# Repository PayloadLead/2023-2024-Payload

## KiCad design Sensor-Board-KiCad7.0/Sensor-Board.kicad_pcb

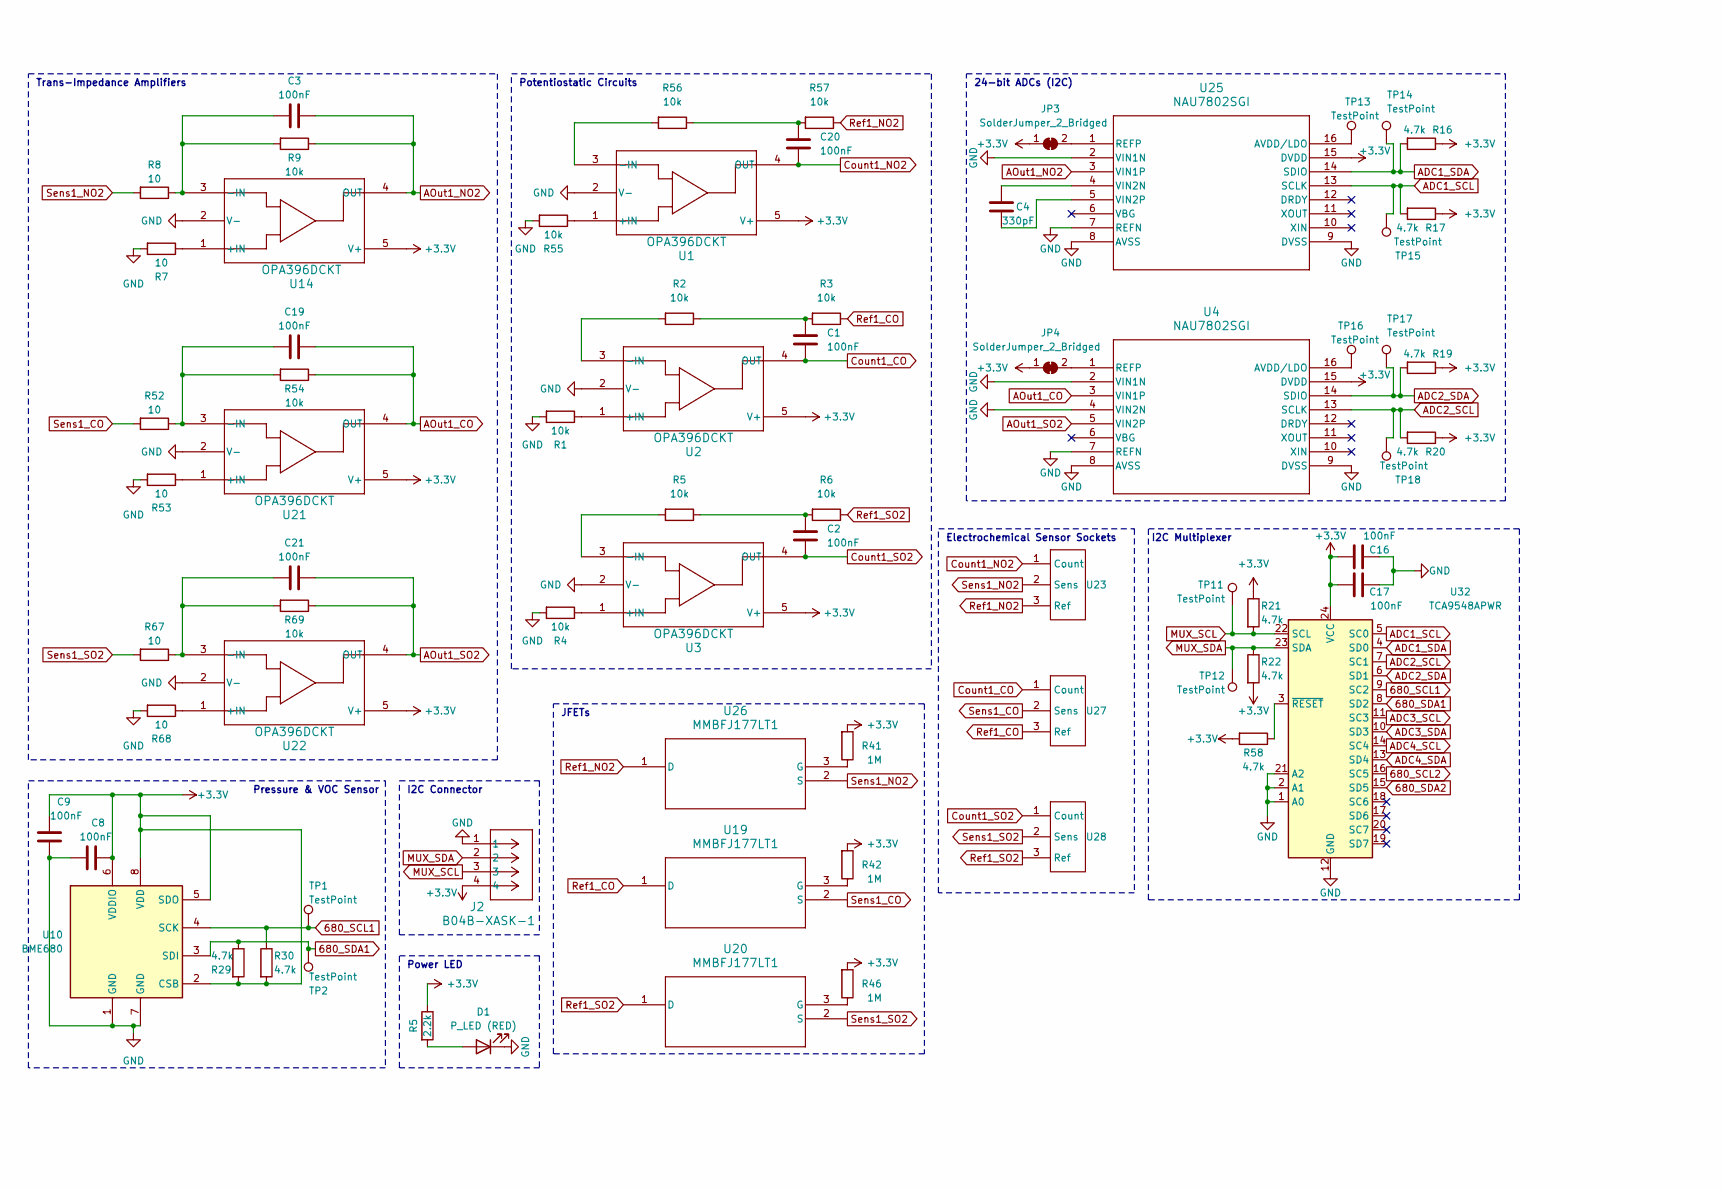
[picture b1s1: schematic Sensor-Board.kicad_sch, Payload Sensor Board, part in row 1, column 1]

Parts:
C1, C2, C3, C8, C9, C16, C17, C19, C20, C21: 100nF; C_0603_1608Metric; LCSC C14663
C4: 330pF; C_0603_1608Metric; LCSC C140966
D1: P_LED (RED); LED_0603_1608Metric_Pad1.05x0.95mm_HandSolder
J2: B04B-XASK-1; CONN_B04B-XASK-1_JST; LCSC C264994
JP3, JP4: SolderJumper_2_Bridged; SolderJumper-2_P1.3mm_Bridged_RoundedPad1.0x1.5mm
R1, R2, R3, R4, R5, R6, R9, R54, R55, R56, R57, R69: 10k; R_0603_1608Metric; LCSC C25804
R7, R8, R52, R53, R67, R68: 10; R_0603_1608Metric; LCSC C22859
R16, R17, R19, R20, R21, R22, R29, R30: 4.7k; R_0603_1608Metric
R41, R42, R46: 1M; R_0603_1608Metric; LCSC C22935
R58: 4.7k; R_0603_1608Metric; LCSC C23162
TP1, TP2, TP11, TP12, TP13, TP14, TP15, TP16, TP17, TP18: TestPoint; TestPoint_Pad_D1.5mm
U1, U2, U3, U14, U21, U22: OPA396DCKT; SC_96DCKT_TEX; Digikey 296-OPA396DCKRCT-ND
U4, U25: NAU7802SGI; SOI16_NAU7802SGI_NUV; Digikey NAU7802SGI-ND
U10: BME680; Bosch_LGA-8_3x3mm_P0.8mm_ClockwisePinNumbering; LCSC C125972
U19, U20, U26: MMBFJ177LT1; SOT-23-3_1P4X3P040_ONS; LCSC C106763
U23: 3-pin socket; Digikey ED90102-ND
U27, U28: 3-pin socket
U32: TCA9548APWR; TSSOP-24_4.4x7.8mm_P0.65mm; LCSC C130026

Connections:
680_SCL1: R30.1, TP1.1, U10.4 (SCK), U32.9 (SC2)
680_SCL2: U32.16 (SC5); also elsewhere on the board
680_SDA1: R29.1, TP2.1, U10.3 (SDI), U32.8 (SD2)
680_SDA2: U32.15 (SD5); also elsewhere on the board
ADC1_SCL: R17.2, TP15.1, U25.13 (SCLK), U32.5 (SC0)
ADC1_SDA: R16.2, TP14.1, U25.14 (SDIO), U32.4 (SD0)
ADC2_SCL: R20.2, TP18.1, U4.13 (SCLK), U32.7 (SC1)
ADC2_SDA: R19.2, TP17.1, U4.14 (SDIO), U32.6 (SD1)
ADC3_SCL: U32.11 (SC3); also elsewhere on the board
ADC3_SDA: U32.10 (SD3); also elsewhere on the board
ADC4_SCL: U32.14 (SC4); also elsewhere on the board
ADC4_SDA: U32.13 (SD4); also elsewhere on the board
AOut1_CO: C19.1, R54.1, U4.3 (VIN1P), U21.4 (OUT)
AOut1_NO2: C3.1, R9.1, U14.4 (OUT), U25.3 (VIN1P)
AOut1_SO2: C21.1, R69.1, U4.5 (VIN2P), U22.4 (OUT)
Count1_CO: C1.2, U2.4 (OUT), U27.1 (Count)
Count1_NO2: C20.2, U1.4 (OUT), U23.1 (Count)
Count1_SO2: C2.2, U3.4 (OUT), U28.1 (Count)
GND: C8.1, C9.2, C16.1, C17.1, D1.1 (K), J2.1, R1.2, R4.2, R7.2, R53.2, R55.2, R68.2, U1.2 (V-), U2.2 (V-), U3.2 (V-), U4.2 (VIN1N), U4.4 (VIN2N), U4.7 (REFN), U4.8 (AVSS), U4.9 (DVSS), U10.1 (GND), U10.7 (GND), U14.2 (V-), U21.2 (V-), U22.2 (V-), U25.2 (VIN1N), U25.7 (REFN), U25.8 (AVSS), U25.9 (DVSS), U32.1 (A0), U32.2 (A1), U32.12 (GND), U32.21 (A2); also elsewhere on the board
MUX_SCL: J2.3, R21.2, TP11.1, U32.22 (SCL)
MUX_SDA: J2.2, R22.1, TP12.1, U32.23 (SDA)
unnamed: C1.1, R2.1, R3.2
unnamed: C20.1, R56.1, R57.2
unnamed: JP3.2 (B), U25.1 (REFP)
unnamed: JP4.2 (B), U4.1 (REFP)
unnamed: R55.1, U1.1 (+IN)
unnamed: R56.2, U1.3 (-IN)
unnamed: R1.1, U2.1 (+IN)
unnamed: R2.2, U2.3 (-IN)
unnamed: R4.1, U3.1 (+IN)
unnamed: TP16.1, U4.16 (AVDD/LDO)
unnamed: R7.1, U14.1 (+IN)
unnamed: C3.2, R8.1, R9.2, U14.3 (-IN)
unnamed: R42.1, U19.3 (G)
unnamed: R46.1, U20.3 (G)
unnamed: R53.1, U21.1 (+IN)
unnamed: C19.2, R52.1, R54.2, U21.3 (-IN)
unnamed: R68.1, U22.1 (+IN)
unnamed: C21.2, R67.1, R69.2, U22.3 (-IN)
unnamed: TP13.1, U25.16 (AVDD/LDO)
unnamed: C4.1, U25.4 (VIN2N)
unnamed: C4.2, U25.5 (VIN2P)
unnamed: R41.1, U26.3 (G)
unnamed: R58.1, U32.3 (~RESET)
Ref1_CO: R3.1, U19.1 (D), U27.3 (Ref)
Ref1_NO2: R57.1, U23.3 (Ref), U26.1 (D)
Ref1_SO2: R6.1, U20.1 (D), U28.3 (Ref)
Sens1_CO: R52.2, U19.2 (S), U27.2 (Sens)
Sens1_NO2: R8.2, U23.2 (Sens), U26.2 (S)
Sens1_SO2: R67.2, U20.2 (S), U28.2 (Sens)

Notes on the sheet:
I2C Connector
JFETs
Electrochemical Sensor Sockets
Power LED
24-bit ADCs (I2C)
Potentiostatic Circuits
I2C Multiplexer
Pressure & VOC Sensor
Trans-Impedance Amplifiers

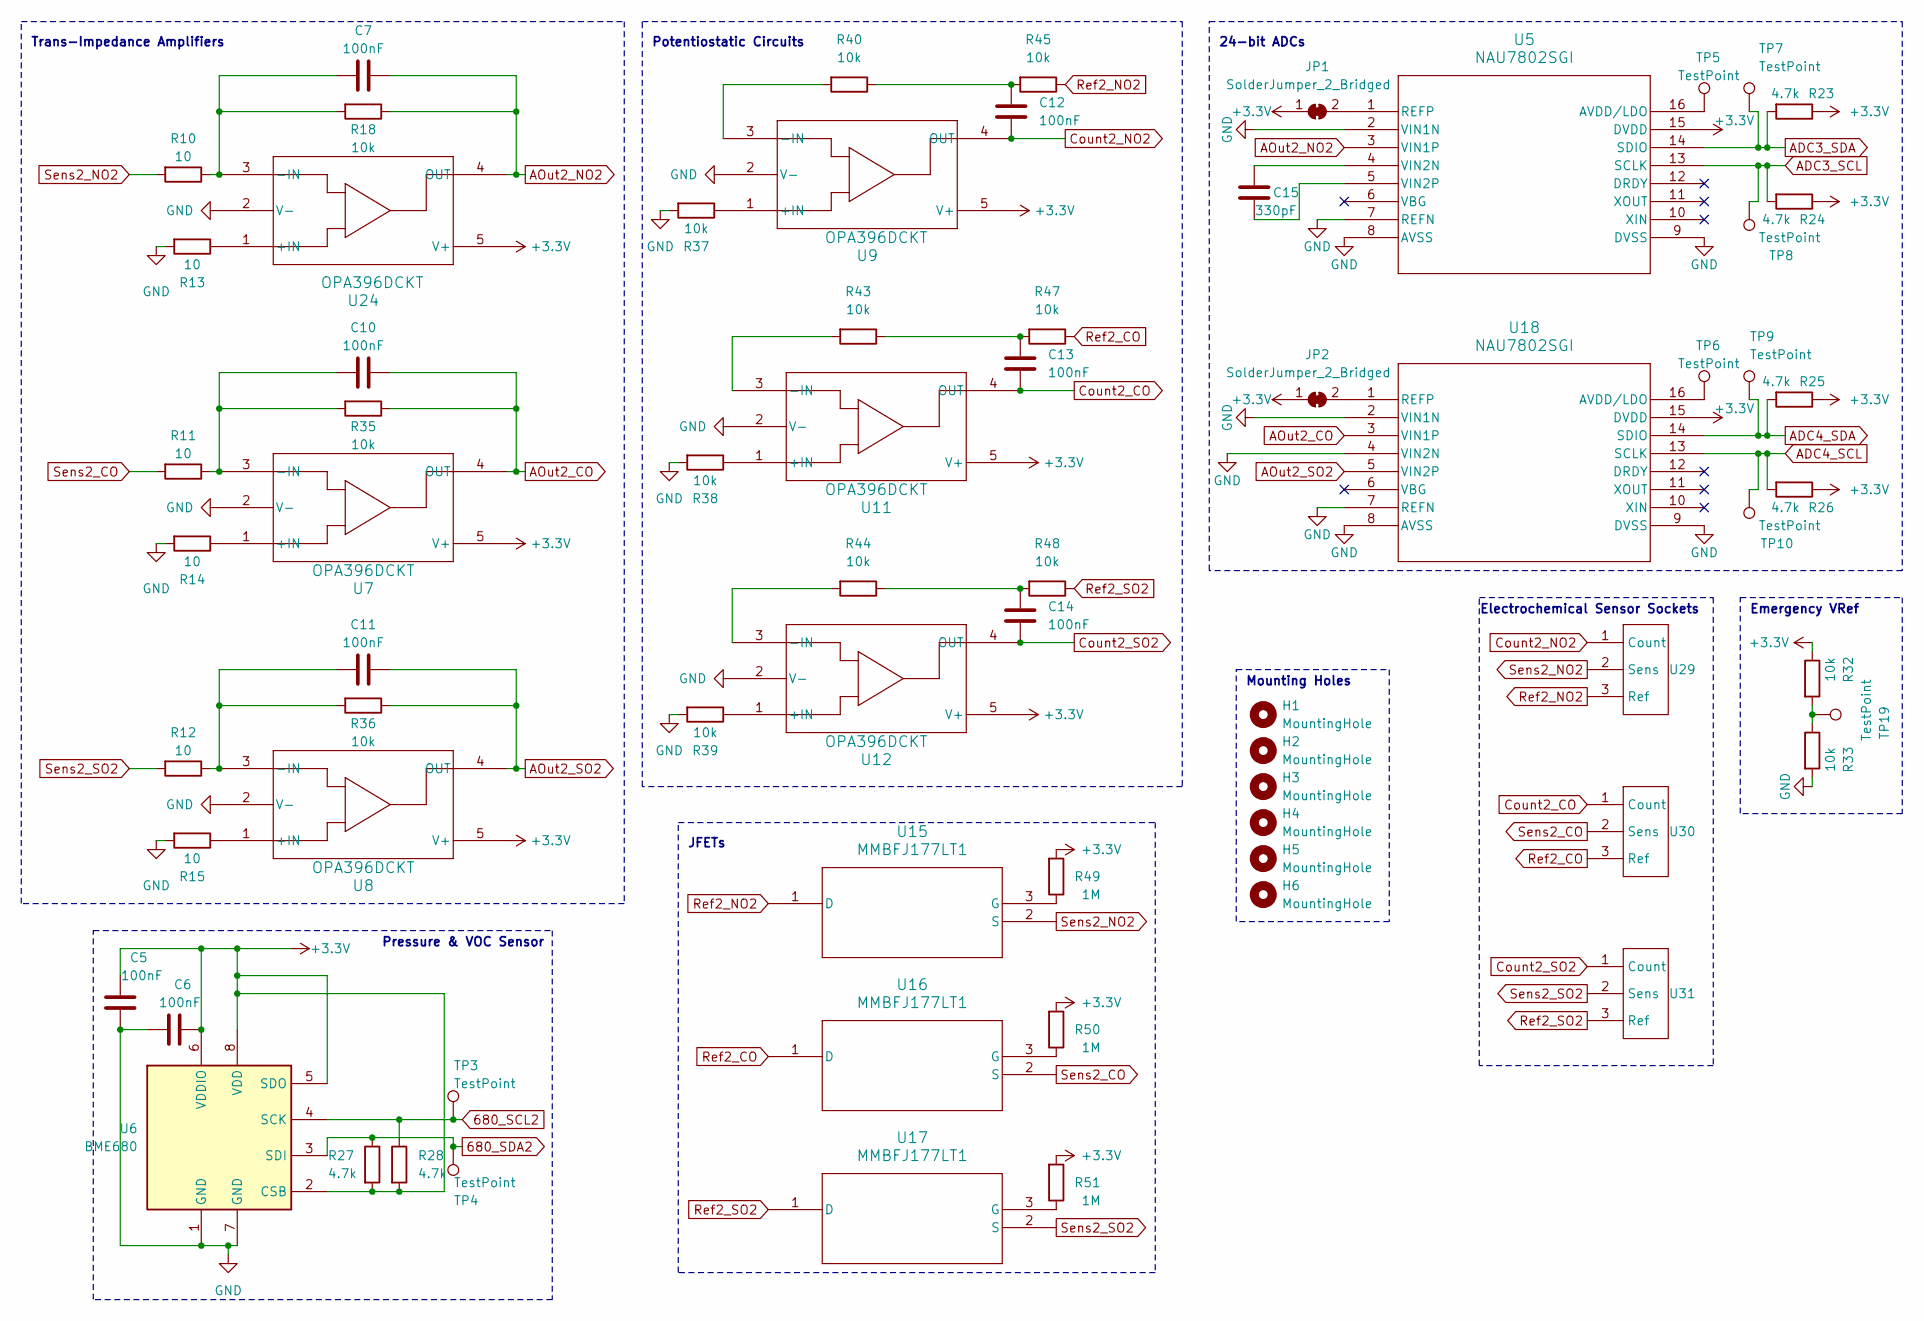
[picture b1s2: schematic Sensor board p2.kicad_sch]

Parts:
C5, C6, C7, C10, C11, C12, C13, C14: 100nF; C_0603_1608Metric; LCSC C14663
C15: 330pF; C_0603_1608Metric; LCSC C140966
H1, H2, H3, H4, H5, H6: MountingHole; Rod_Mounting_Hole_6.7564mm
JP1, JP2: SolderJumper_2_Bridged; SolderJumper-2_P1.3mm_Bridged_RoundedPad1.0x1.5mm
R10, R11, R12, R13, R14, R15: 10; R_0603_1608Metric; LCSC C22859
R18, R35, R36, R37, R38, R39, R40, R43, R44, R45, R47, R48: 10k; R_0603_1608Metric; LCSC C25804
R23, R24, R25, R26, R27, R28: 4.7k; R_0603_1608Metric
R32, R33: 10k; R_0603_1608Metric
R49, R50, R51: 1M; R_0603_1608Metric; LCSC C22935
TP3, TP4, TP5, TP6, TP7, TP8, TP9, TP10, TP19: TestPoint; TestPoint_Pad_D1.5mm
U5, U18: NAU7802SGI; SOI16_NAU7802SGI_NUV; Digikey NAU7802SGI-ND
U6: BME680; Bosch_LGA-8_3x3mm_P0.8mm_ClockwisePinNumbering; LCSC C125972
U7, U8, U9, U11, U12, U24: OPA396DCKT; SC_96DCKT_TEX; Digikey 296-OPA396DCKRCT-ND
U15, U16, U17: MMBFJ177LT1; SOT-23-3_1P4X3P040_ONS; LCSC C106763
U29, U30, U31: 3-pin socket; Digikey ED90102-ND

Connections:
680_SCL2: R28.1, TP3.1, U6.4 (SCK); also elsewhere on the board
680_SDA2: R27.1, TP4.1, U6.3 (SDI); also elsewhere on the board
ADC3_SCL: R24.2, TP8.1, U5.13 (SCLK); also elsewhere on the board
ADC3_SDA: R23.2, TP7.1, U5.14 (SDIO); also elsewhere on the board
ADC4_SCL: R26.2, TP10.1, U18.13 (SCLK); also elsewhere on the board
ADC4_SDA: R25.2, TP9.1, U18.14 (SDIO); also elsewhere on the board
AOut2_CO: C10.1, R35.1, U7.4 (OUT), U18.3 (VIN1P)
AOut2_NO2: C7.1, R18.1, U5.3 (VIN1P), U24.4 (OUT)
AOut2_SO2: C11.1, R36.1, U8.4 (OUT), U18.5 (VIN2P)
Count2_CO: C13.2, U11.4 (OUT), U30.1 (Count)
Count2_NO2: C12.2, U9.4 (OUT), U29.1 (Count)
Count2_SO2: C14.2, U12.4 (OUT), U31.1 (Count)
GND: C5.2, C6.1, R13.2, R14.2, R15.2, R33.2, R37.2, R38.2, R39.2, U5.2 (VIN1N), U5.7 (REFN), U5.8 (AVSS), U5.9 (DVSS), U6.1 (GND), U6.7 (GND), U7.2 (V-), U8.2 (V-), U9.2 (V-), U11.2 (V-), U12.2 (V-), U18.2 (VIN1N), U18.4 (VIN2N), U18.7 (REFN), U18.8 (AVSS), U18.9 (DVSS), U24.2 (V-); also elsewhere on the board
unnamed: C12.1, R40.1, R45.2
unnamed: C13.1, R43.1, R47.2
unnamed: C14.1, R44.1, R48.2
unnamed: JP1.2 (B), U5.1 (REFP)
unnamed: JP2.2 (B), U18.1 (REFP)
unnamed: R32.2, R33.1, TP19.1
unnamed: TP5.1, U5.16 (AVDD/LDO)
unnamed: C15.1, U5.4 (VIN2N)
unnamed: C15.2, U5.5 (VIN2P)
unnamed: R14.1, U7.1 (+IN)
unnamed: C10.2, R11.1, R35.2, U7.3 (-IN)
unnamed: R15.1, U8.1 (+IN)
unnamed: C11.2, R12.1, R36.2, U8.3 (-IN)
unnamed: R37.1, U9.1 (+IN)
unnamed: R40.2, U9.3 (-IN)
unnamed: R38.1, U11.1 (+IN)
unnamed: R43.2, U11.3 (-IN)
unnamed: R39.1, U12.1 (+IN)
unnamed: R44.2, U12.3 (-IN)
unnamed: R49.1, U15.3 (G)
unnamed: R50.1, U16.3 (G)
unnamed: R51.1, U17.3 (G)
unnamed: TP6.1, U18.16 (AVDD/LDO)
unnamed: R13.1, U24.1 (+IN)
unnamed: C7.2, R10.1, R18.2, U24.3 (-IN)
Ref2_CO: R47.1, U16.1 (D), U30.3 (Ref)
Ref2_NO2: R45.1, U15.1 (D), U29.3 (Ref)
Ref2_SO2: R48.1, U17.1 (D), U31.3 (Ref)
Sens2_CO: R11.2, U16.2 (S), U30.2 (Sens)
Sens2_NO2: R10.2, U15.2 (S), U29.2 (Sens)
Sens2_SO2: R12.2, U17.2 (S), U31.2 (Sens)

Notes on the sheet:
JFETs
Potentiostatic Circuits
24-bit ADCs
Emergency VRef
Electrochemical Sensor Sockets
Pressure & VOC Sensor
Trans-Impedance Amplifiers
Mounting Holes

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
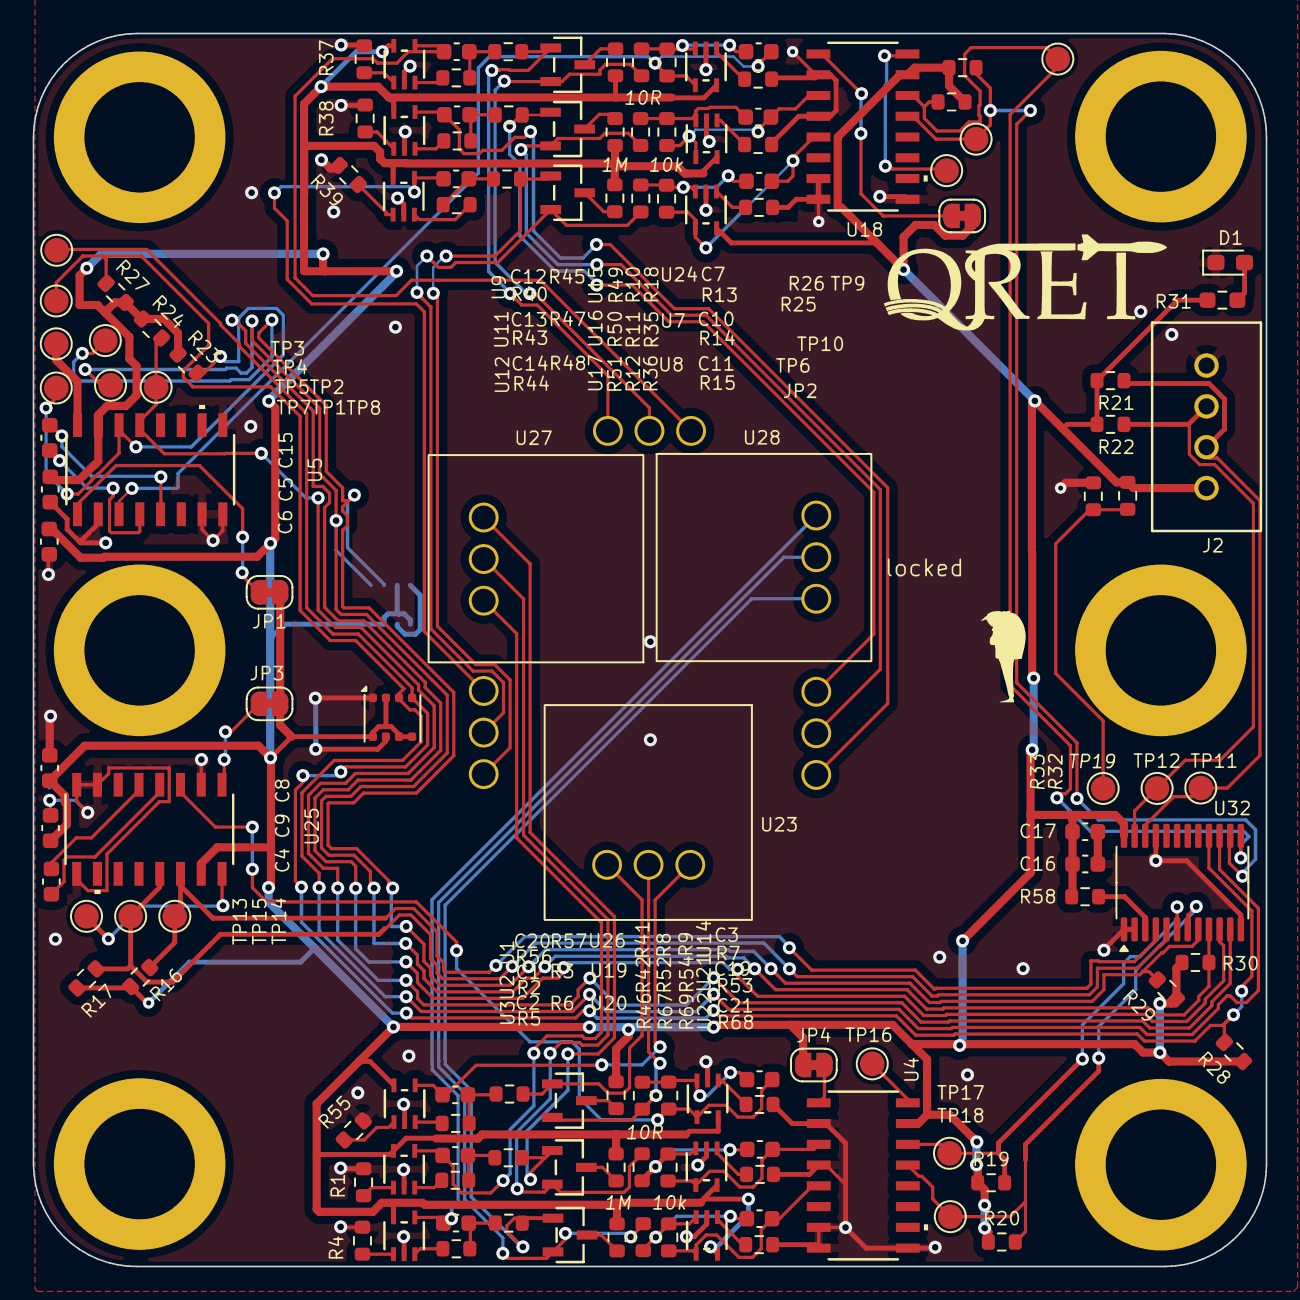
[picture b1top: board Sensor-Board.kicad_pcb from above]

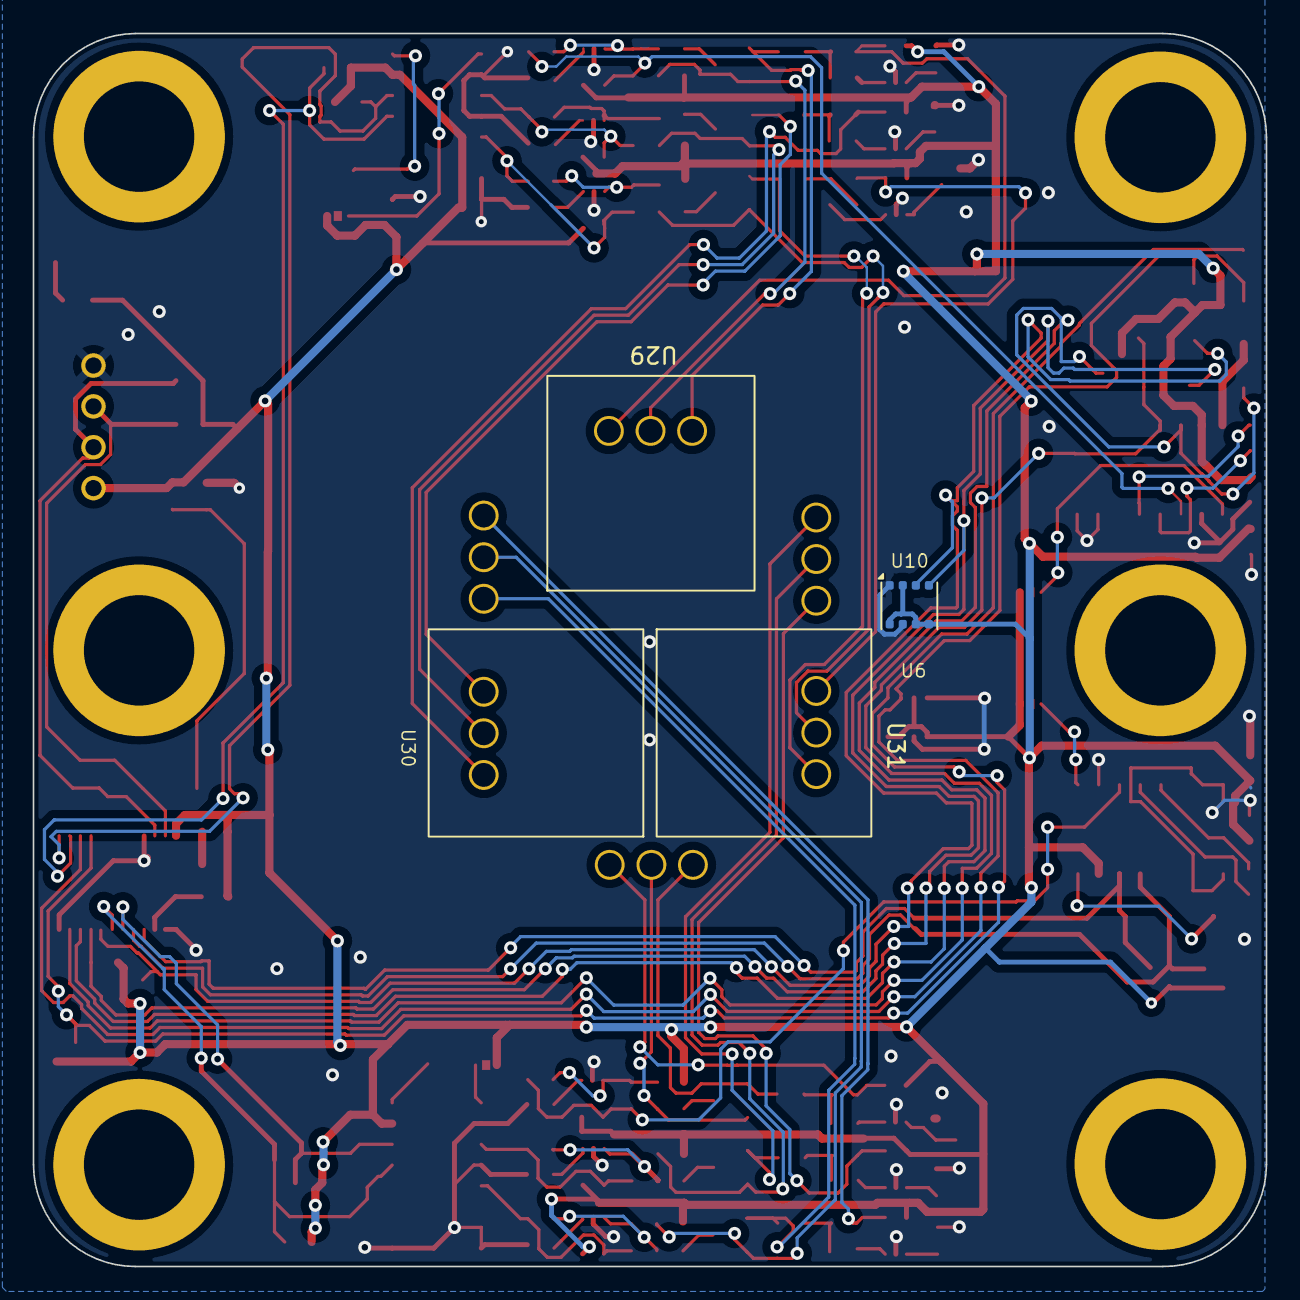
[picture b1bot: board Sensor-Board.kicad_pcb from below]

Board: 2 copper layers, 75.4 x 75.4 mm, 142 parts (4 on the bottom side), 91 nets.

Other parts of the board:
R31: 2.2k; R_0603_1608Metric_Pad0.98x0.95mm_HandSolder

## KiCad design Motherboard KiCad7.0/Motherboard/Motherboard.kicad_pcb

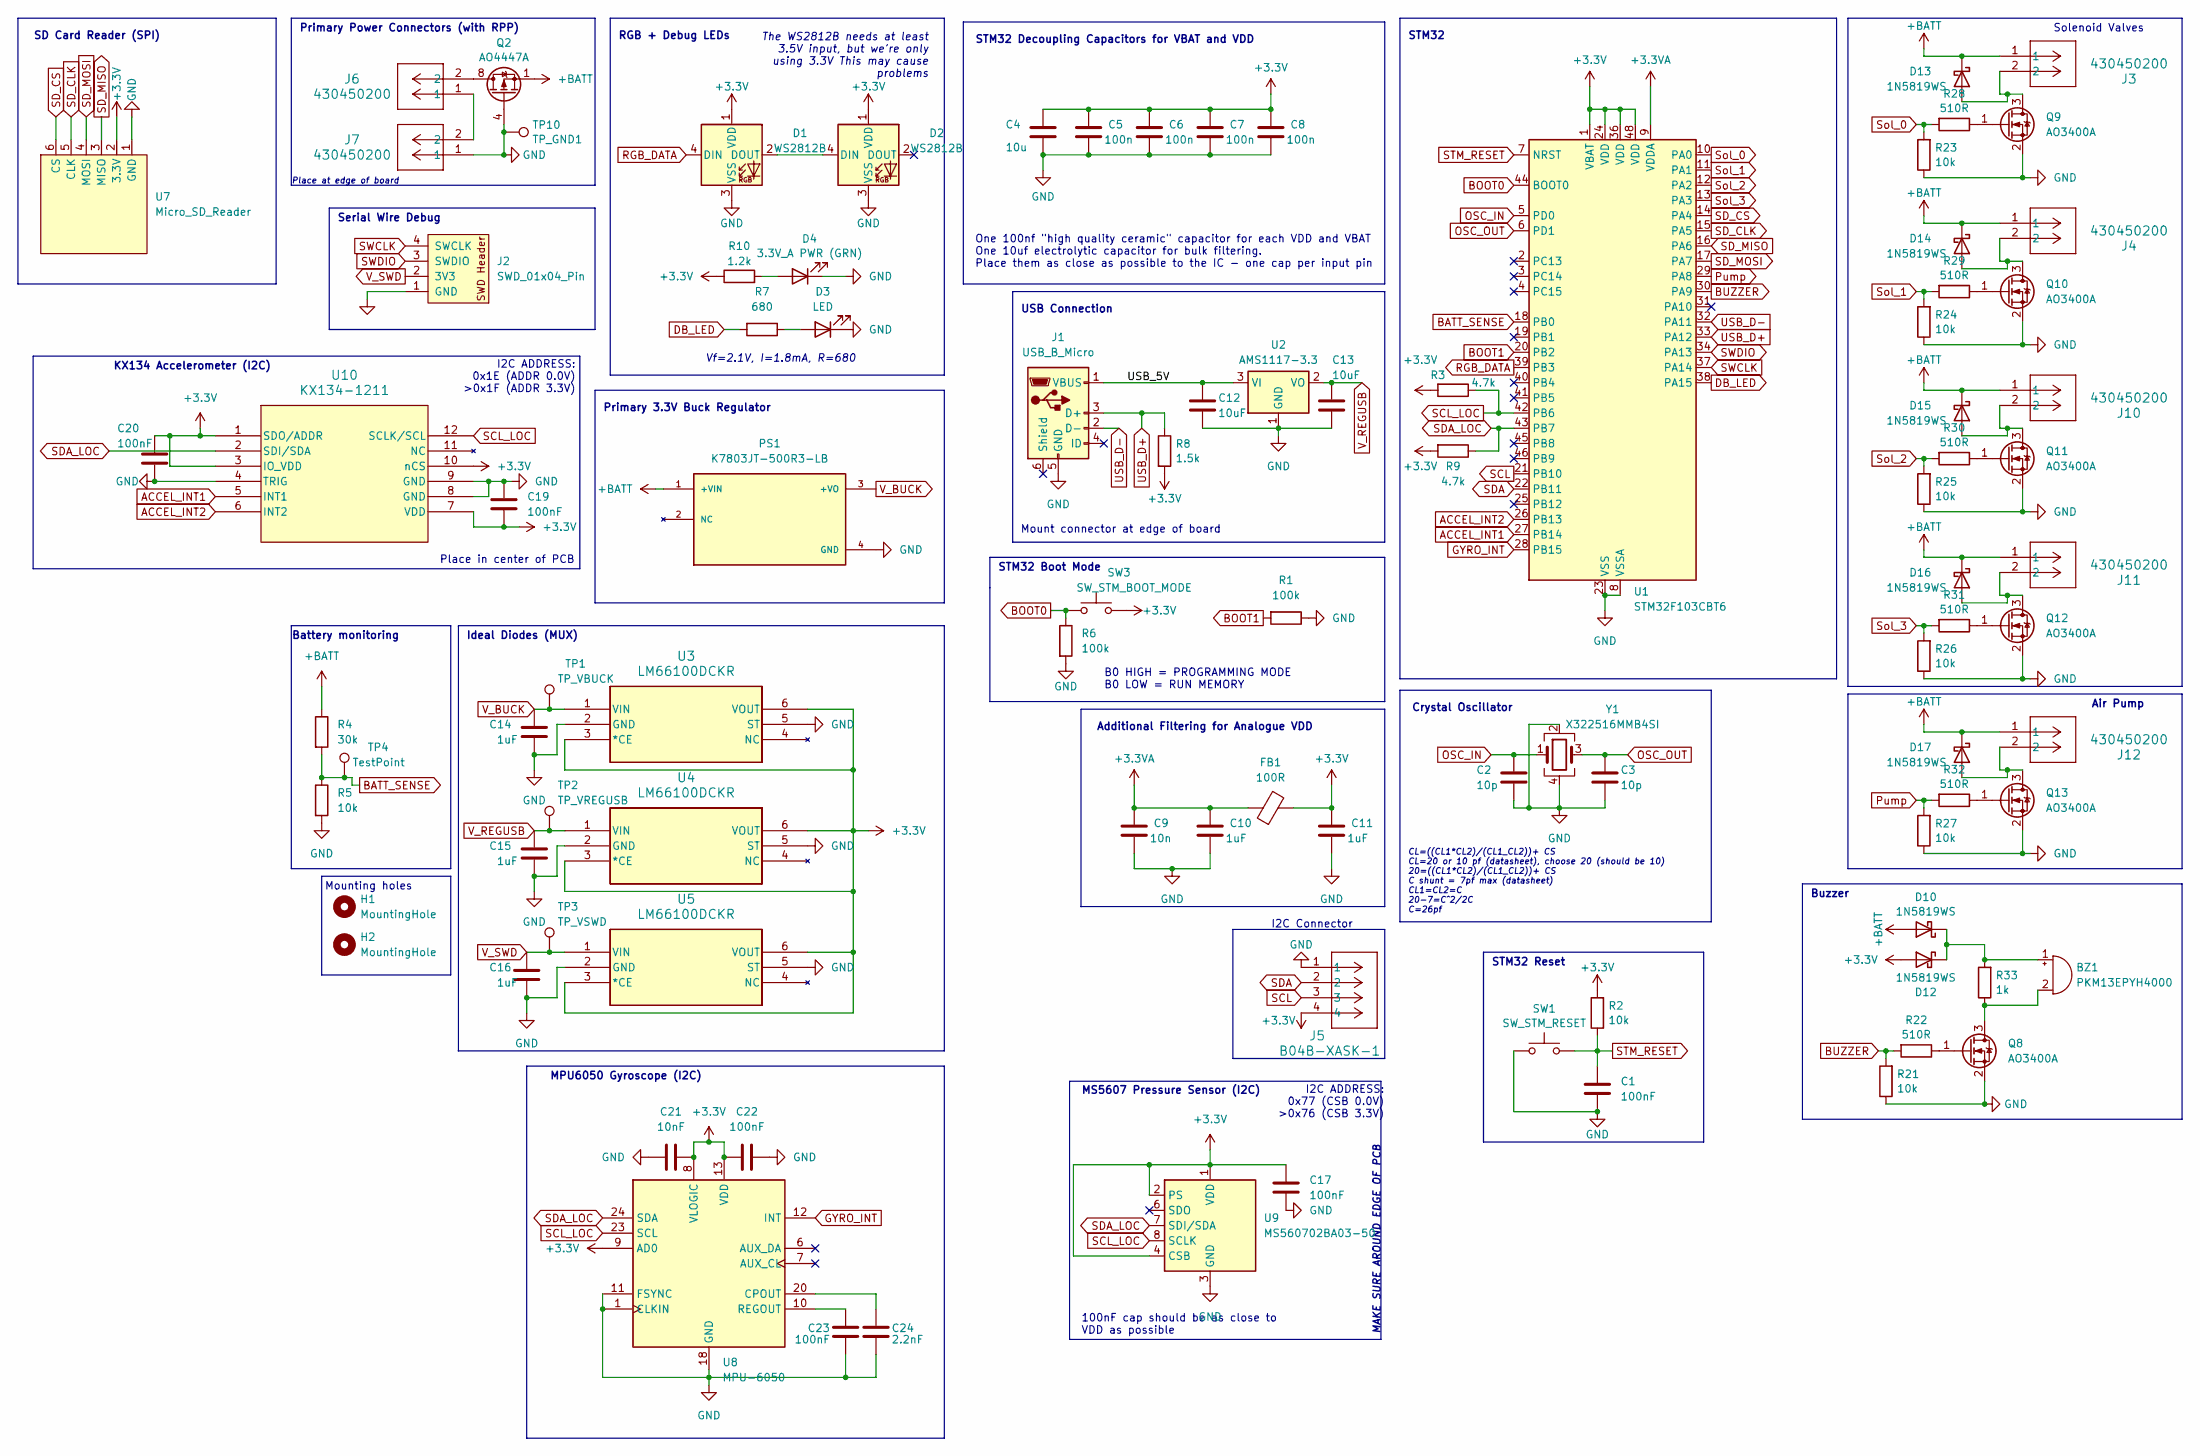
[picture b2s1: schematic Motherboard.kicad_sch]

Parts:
BZ1: PKM13EPYH4000; Buzzer_12.6x9.5RM5.0; Digikey 490-4698-1-ND
C1, C17, C19, C20, C22, C23: 100nF; C_0603_1608Metric; LCSC C14663
C2, C3: 10p; C_0603_1608Metric; LCSC C1634
C4: 10u; CP_Elec_4x5.4; Digikey 732-8411-1-ND
C5, C6, C7, C8: 100n; C_0402_1005Metric; LCSC C1525
C9: 10n; C_0603_1608Metric; LCSC C57112
C10, C11: 1uF; C_0805_2012Metric; LCSC C28323
C12, C13: 10uF; C_0603_1608Metric; LCSC C96446
C14, C15, C16: 1uF; C_0603_1608Metric; LCSC C15849
C21: 10nF; C_0603_1608Metric; LCSC C57112
C24: 2.2nF; C_0603_1608Metric; LCSC C1604
D1, D2: WS2812B; LED_WS2812B_PLCC4_5.0x5.0mm_P3.2mm; Digikey 1568-COM-16347CT-ND
D3: LED; LED_0603_1608Metric; LCSC C72038
D4: 3.3V_A PWR (GRN); LED_0805_2012Metric; LCSC C2297
D10, D12, D13, D14, D15, D16, D17: 1N5819WS; D_SOD-323; LCSC C191023
FB1: 100R; R_0805_2012Metric; LCSC C1015
H1, H2: MountingHole; Rod_Mounting_Hole_6.7564mm
J1: USB_B_Micro; USB_Micro-B_Amphenol_10118194_Horizontal; LCSC C132563
J2: SWD_01x04_Pin; SWD_PinHeader_1x04_P2.54mm_Horizontal; Digikey 2057-PH1RB-04-UA-ND
J3, J4, J6, J7, J10, J11, J12: 430450200; CON_430450200_MOL; LCSC C122431
J5: B04B-XASK-1; CONN_B04B-XASK-1_JST; Digikey 455-B04B-XASK-1-ND
PS1: K7803JT-500R3-LB; K78_JT-500R3_MNS; PARTREV 2022.07.25-A/4; Digikey 2725-K7803JT-500R3-LBCT-ND
Q2: AO4447A; SOIC-8_3.9x4.9mm_P1.27mm; LCSC C125867
Q8, Q9, Q10, Q11, Q12, Q13: AO3400A; SOT-23; LCSC C20917
R1, R6: 100k; R_0603_1608Metric; LCSC C25803
R2, R5, R21, R23, R24, R25, R26, R27: 10k; R_0603_1608Metric; LCSC C25804
R3, R9: 4.7k; R_0603_1608Metric; LCSC C23162
R4: 30k; R_0603_1608Metric; LCSC C22984
R7: 680; R_0603_1608Metric; LCSC C23228
R8: 1.5k; R_0603_1608Metric; LCSC C22843
R10: 1.2k; R_0603_1608Metric; LCSC C22765
R22, R28, R29, R30, R31, R32: 510R; R_0603_1608Metric; LCSC C23193
R33: 1k; R_0603_1608Metric; LCSC C21190
SW1: SW_STM_RESET; SW_Push_1P1T_XKB_TS-1187A; LCSC C318884
SW3: SW_STM_BOOT_MODE; SW_Push_1P1T_XKB_TS-1187A; LCSC C318884
TP1: TP_VBUCK; TestPoint_Pad_1.5x1.5mm
TP2: TP_VREGUSB; TestPoint_Pad_1.5x1.5mm
TP3: TP_VSWD; TestPoint_Pad_1.5x1.5mm
TP4: TestPoint; TestPoint_Pad_1.0x1.0mm
TP10: TP_GND1; TestPoint_Pad_2.0x2.0mm
U1: STM32F103CBT6; LQFP-48_7x7mm_P0.5mm; LCSC C8304
U2: AMS1117-3.3; SOT-223-3_TabPin2; LCSC C6186
U3, U4, U5: LM66100DCKR; SC-70-6_Handsoldering; LCSC C2869734
U7: Micro_SD_Reader; MicroSD Card Reader
U8: MPU-6050; InvenSense_QFN-24_4x4mm_P0.5mm; LCSC C24112
U9: MS560702BA03-50; MS5607_Handsolder; Digikey 223-1198-1-ND
U10: KX134-1211; LGA-12_2x2mm_P0.5mm; LCSC C2157908
Y1: X322516MMB4SI; Crystal_SMD_3225-4Pin_3.2x2.5mm; LCSC C13738

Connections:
+3.3V: C4.1, C5.1, C6.1, C7.1, C8.1, C11.1, C17.1, C19.2, C20.1, C21.2, C22.1, D1.1 (VDD), D2.1 (VDD), D12.2 (A), FB1.2, J5.4, R2.2, R3.2, R8.2, R9.2, R10.1, SW3.3 (B), SW3.4 (B), U1.1 (VBAT), U1.24 (VDD), U1.36 (VDD), U1.48 (VDD), U3.3 (*CE), U3.6 (VOUT), U4.3 (*CE), U4.6 (VOUT), U5.3 (*CE), U5.6 (VOUT), U7.2 (3.3V), U8.8 (VLOGIC), U8.9 (AD0), U8.13 (VDD), U9.1 (VDD), U9.2 (PS), U9.4 (CSB), U9.5 (CSB), U10.1 (SDO/ADDR), U10.3 (IO_VDD), U10.7 (VDD), U10.10 (nCS)
+3.3VA: C9.1, C10.1, FB1.1, U1.9 (VDDA)
+BATT: D10.2 (A), D13.1 (K), D14.1 (K), D15.1 (K), D16.1 (K), D17.1 (K), J3.1, J4.1, J10.1, J11.1, J12.1, PS1.1 (+VIN), Q2.1 (S), Q2.2 (S), Q2.3 (S), R4.1
/USB_5V: C12.1, J1.1 (VBUS), U2.3 (VI)
ACCEL_INT1: U1.27 (PB14), U10.5 (INT1)
ACCEL_INT2: U1.26 (PB13), U10.6 (INT2)
BATT_SENSE: R4.2, R5.1, TP4.1, U1.18 (PB0)
BOOT0: R6.1, SW3.1 (A), SW3.2 (A), U1.44 (BOOT0)
BOOT1: R1.2, U1.20 (PB2)
BUZZER: R21.2, R22.2, U1.30 (PA9)
DB_LED: R7.2, U1.38 (PA15)
GND: C1.2, C2.2, C3.2, C4.2, C5.2, C6.2, C7.2, C8.2, C9.2, C10.2, C11.2, C12.2, C13.2, C14.2, C15.2, C16.2, C17.2, C19.1, C20.2, C21.1, C22.2, C23.2, C24.2, D1.3 (VSS), D2.3 (VSS), D3.1 (K), D4.1 (K), J1.5 (GND), J2.1 (GND), J5.1, J7.1, PS1.4 (GND), Q2.4 (G), Q8.2 (S), Q9.2 (S), Q10.2 (S), Q11.2 (S), Q12.2 (S), Q13.2 (S), R1.1, R5.2, R6.2, R21.1, R23.1, R24.1, R25.1, R26.1, R27.1, SW1.1, TP10.1, U1.8 (VSSA), U1.23 (VSS), U1.35 (VSS), U1.47 (VSS), U2.1 (GND), U3.2 (GND), U3.5 (ST), U4.2 (GND), U4.5 (ST), U5.2 (GND), U5.5 (ST), U7.1 (GND), U8.1 (CLKIN), U8.11 (FSYNC), U8.18 (GND), U9.3 (GND), U10.4 (TRIG), U10.8 (GND), U10.9 (GND), Y1.2, Y1.4
GYRO_INT: U1.28 (PB15), U8.12 (INT)
unnamed: BZ1.1 (+), D10.1 (K), D12.1 (K), R33.2
unnamed: BZ1.2 (-), Q8.3 (D), R33.1
unnamed: D1.2 (DOUT), D2.4 (DIN)
unnamed: D3.2 (A), R7.1
unnamed: D4.2 (A), R10.2
unnamed: D13.2 (A), J3.2, Q9.3 (D)
unnamed: D14.2 (A), J4.2, Q10.3 (D)
unnamed: D15.2 (A), J10.2, Q11.3 (D)
unnamed: D16.2 (A), J11.2, Q12.3 (D)
unnamed: D17.2 (A), J12.2, Q13.3 (D)
unnamed: J6.1, J7.2
unnamed: J6.2, Q2.5 (D), Q2.6 (D), Q2.7 (D), Q2.8 (D)
unnamed: Q8.1 (G), R22.1
unnamed: Q9.1 (G), R28.1
unnamed: Q10.1 (G), R29.1
unnamed: Q11.1 (G), R30.1
unnamed: Q12.1 (G), R31.1
unnamed: Q13.1 (G), R32.1
unnamed: C24.1, U8.20 (CPOUT)
unnamed: C23.1, U8.10 (REGOUT)
OSC_IN: C2.1, U1.5 (PD0), Y1.1
OSC_OUT: C3.1, U1.6 (PD1), Y1.3
Pump: R27.2, R32.2, U1.29 (PA8)
RGB_DATA: D1.4 (DIN), U1.39 (PB3)
SCL: J5.3, U1.21 (PB10)
SCL_LOC: R3.1, U1.42 (PB6), U8.23 (SCL), U9.8 (SCLK), U10.12 (SCLK/SCL)
SDA: J5.2, U1.22 (PB11)
SDA_LOC: R9.1, U1.43 (PB7), U8.24 (SDA), U9.7 (SDI/SDA), U10.2 (SDI/SDA)
SD_CLK: U1.15 (PA5), U7.5 (CLK)
SD_CS: U1.14 (PA4), U7.6 (CS)
SD_MISO: U1.16 (PA6), U7.3 (MISO)
SD_MOSI: U1.17 (PA7), U7.4 (MOSI)
STM_RESET: C1.1, R2.1, SW1.2, U1.7 (NRST)
SWCLK: J2.4 (SWCLK), U1.37 (PA14)
SWDIO: J2.3 (SWDIO), U1.34 (PA13)
Sol_0: R23.2, R28.2, U1.10 (PA0)
Sol_1: R24.2, R29.2, U1.11 (PA1)
Sol_2: R25.2, R30.2, U1.12 (PA2)
Sol_3: R26.2, R31.2, U1.13 (PA3)
USB_D+: J1.3 (D+), R8.1, U1.33 (PA12)
USB_D-: J1.2 (D-), U1.32 (PA11)
V_BUCK: C14.1, PS1.3 (+VO), TP1.1, U3.1 (VIN)
V_REGUSB: C13.1, C15.1, TP2.1, U2.2 (VO), U4.1 (VIN)
V_SWD: C16.1, J2.2 (3V3), TP3.1, U5.1 (VIN)

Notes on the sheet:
SD Card Reader (SPI)
MAKE SURE AROUND EDGE OF PCB
100nF cap should be as close to VDD as possible
USB Connection
I2C Connector
Place in center of PCB
Solenoid Valves
STM32 Decoupling Capacitors for VBAT and VDD
Buzzer
CL=((CL1*CL2)/(CL1_CL2))+ CS CL=20 or 10 pf (datasheet), choose 20 (should be 10) 20=((CL1*CL2)/(CL1_CL2))+ CS C shunt = 7pf max (datasheet) CL1=CL2=C 20-7=C^2/2C C=26pf
STM32
STM32 Boot Mode
Primary 3.3V Buck Regulator
The WS2812B needs at least 3.5V input, but we're only using 3.3V This may cause problems
Mount connector at edge of board
Vf=2.1V, I=1.8mA, R=680
One 100nf "high quality ceramic" capacitor for each VDD and VBAT One 10uf electrolytic capacitor for bulk filtering. Place them as close as possible to the IC - one cap per input pin
STM32 Reset
Serial Wire Debug
I2C ADDRESS: 0x77 (CSB 0.0V) >0x76 (CSB 3.3V)
Primary Power Connectors (with RPP)
RGB + Debug LEDs
Crystal Oscillator
MS5607 Pressure Sensor (I2C)
Ideal Diodes (MUX)
Air Pump
I2C ADDRESS: 0x1E (ADDR 0.0V) >0x1F (ADDR 3.3V)
Additional Filtering for Analogue VDD
KX134 Accelerometer (I2C)
Battery monitoring
Mounting holes
Place at edge of board
MPU6050 Gyroscope (I2C)
B0 HIGH = PROGRAMMING MODE B0 LOW = RUN MEMORY

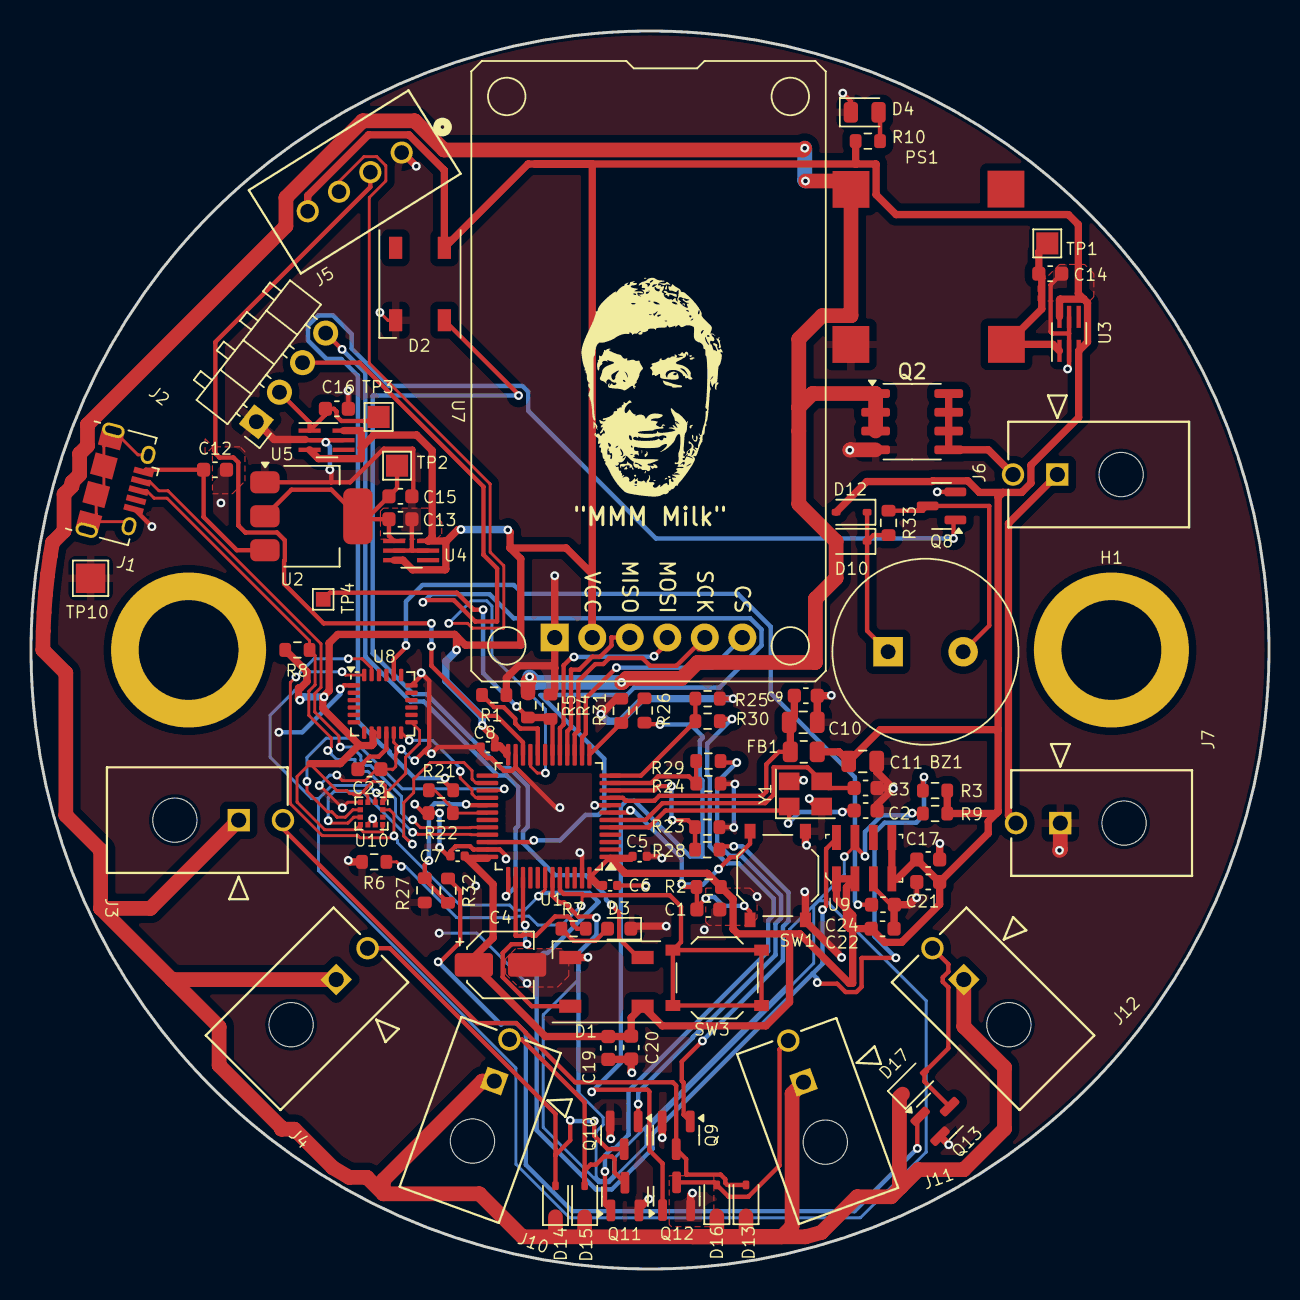
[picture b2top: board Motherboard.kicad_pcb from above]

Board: 2 copper layers, 83.8 x 83.8 mm, 96 parts (0 on the bottom side), 57 nets.
